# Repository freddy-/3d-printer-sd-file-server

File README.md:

# ESP8266 SD Card File Server For 3D Printer

This project mimics the file upload endpoint of OctoPrint allowing to send gcode from prusa slicer and saving direct to SD card.

It is based on ardyesp/ESPWebDAV and FYSETC/ESPWebDAV.
 
SD card is shared between ESP8266 (SPI) and 3d printer (SDIO) running Marlin firmware with a custom change. 

The ESP8266 control the SD Card detection pin from the 3D Printer board. When it receive a file upload it simulate a SD card removal from the 3D Printer and then initialize the SD Card in SPI mode. When the file upload is done it performs a power cycle of the SD Card, otherwise the SD Card wont work in SDIO mode.

This change in Marlin allow the SDIO lines from the SD card to be shared with the ESP8266. When the card is removed from the 3D Printer Marlin detects and disable the SDIO hardware and set these pins to input.

### 3D Printer
The tests were made using a Kingroon KP3S. This printer have a MakerBase Robin Nano clone board with a connector for a external SD board.

### Firmware update
Firmware update can be done via browser through url `<esp-ip>/update`

### Dependencies
- [ESP8266 Arduino](https://github.com/esp8266/Arduino)  version 3.1.2

<div style="display: flex;">

</div>

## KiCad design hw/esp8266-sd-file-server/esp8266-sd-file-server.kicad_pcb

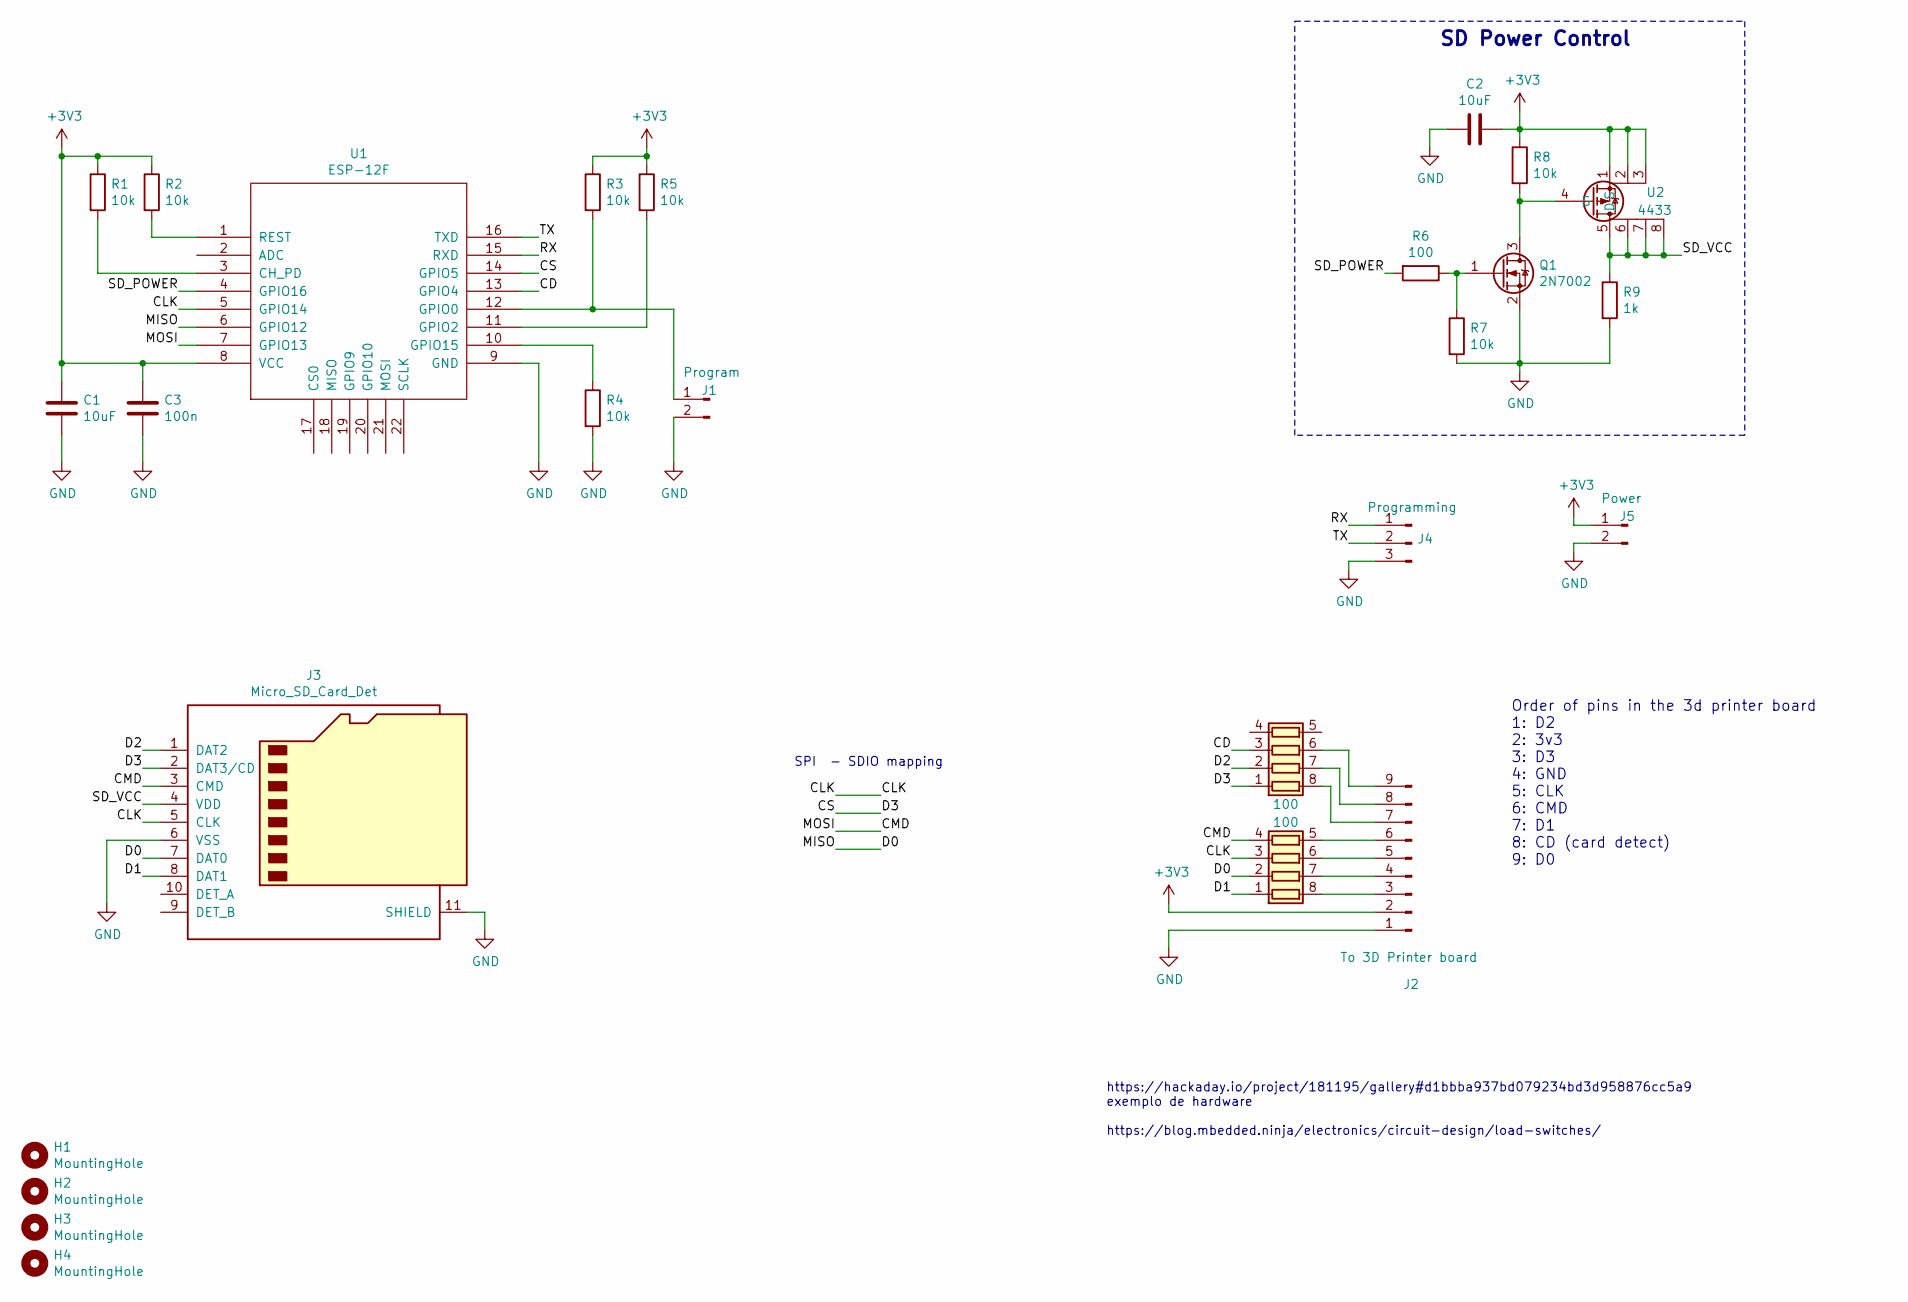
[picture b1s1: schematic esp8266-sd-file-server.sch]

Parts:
C1, C2: 10uF; C_1210_3225Metric_Pad1.42x2.65mm_HandSolder
C3: 100n; C_0805_2012Metric_Pad1.15x1.40mm_HandSolder
H1, H2, H3, H4: MountingHole; MountingHole_3mm
J1: Program; PinHeader_1x02_P2.54mm_Vertical
J2: To 3D Printer board; PinHeader_1x09_P2.54mm_Vertical
J3: Micro_SD_Card_Det; micro_sd
J4: Programming; PinHeader_1x03_P2.54mm_Vertical
J5: Power; PinHeader_1x02_P2.54mm_Vertical
Q1: 2N7002; SOT-23
R1, R2, R3, R4, R5, R7, R8: 10k; R_0603_1608Metric_Pad1.05x0.95mm_HandSolder
R6: 100; R_0603_1608Metric_Pad1.05x0.95mm_HandSolder
R9: 1k; R_0603_1608Metric_Pad1.05x0.95mm_HandSolder
RN1, RN2: 100; R_Array_Convex_4x0603
U1: ESP-12F; ESP-12E_SMD
U2: 4433; SOIC-8_3.9x4.9mm_P1.27mm

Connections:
+3V3: C1.2, C2.1, C3.2, J2.2, J5.1, R1.1, R2.1, R3.1, R5.1, R8.1, U1.8 (VCC), U2.1 (S), U2.2, U2.3
/CD: RN2.3 (R3.1), U1.13 (GPIO4)
/CLK: J3.5 (CLK), RN1.3 (R3.1), U1.5 (GPIO14)
/CMD: J3.3 (CMD), RN1.4 (R4.1), U1.7 (GPIO13)
/CS: J3.2 (DAT3/CD), RN2.1 (R1.1), U1.14 (GPIO5)
/D0: J3.7 (DAT0), RN1.2 (R2.1), U1.6 (GPIO12)
/D1: J3.8 (DAT1), RN1.1 (R1.1)
/D2: J3.1 (DAT2), RN2.2 (R2.1)
/RX: J4.1, U1.15 (RXD)
/SD_POWER: R6.2, U1.4 (GPIO16)
/SD_VCC: J3.4 (VDD), R9.1, U2.5 (D), U2.6, U2.7, U2.8
/TX: J4.2, U1.16 (TXD)
GND: C1.1, C2.2, C3.1, J1.2, J2.1, J3.6 (VSS), J3.11 (SHIELD), J4.3, J5.2, Q1.2 (S), R4.2, R7.2, R9.2, U1.9 (GND)
unnamed: J1.1, R3.2, U1.12 (GPIO0)
unnamed: J2.3, RN1.8 (R1.2)
unnamed: J2.4, RN1.7 (R2.2)
unnamed: J2.5, RN1.6 (R3.2)
unnamed: J2.6, RN1.5 (R4.2)
unnamed: J2.7, RN2.8 (R1.2)
unnamed: J2.8, RN2.7 (R2.2)
unnamed: J2.9, RN2.6 (R3.2)
unnamed: Q1.1 (G), R6.1, R7.1
unnamed: Q1.3 (D), R8.2, U2.4 (G)
unnamed: R1.2, U1.3 (CH_PD)
unnamed: R2.2, U1.1 (REST)
unnamed: R4.1, U1.10 (GPIO15)
unnamed: R5.2, U1.11 (GPIO2)

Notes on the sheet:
SD Power Control
https://hackaday.io/project/181195/gallery#d1bbba937bd079234bd3d958876cc5a9 exemplo de hardware https://blog.mbedded.ninja/electronics/circuit-design/load-switches/
SPI - SDIO mapping
Order of pins in the 3d printer board 1: D2 2: 3v3 3: D3 4: GND 5: CLK 6: CMD 7: D1 8: CD (card detect) 9: D0

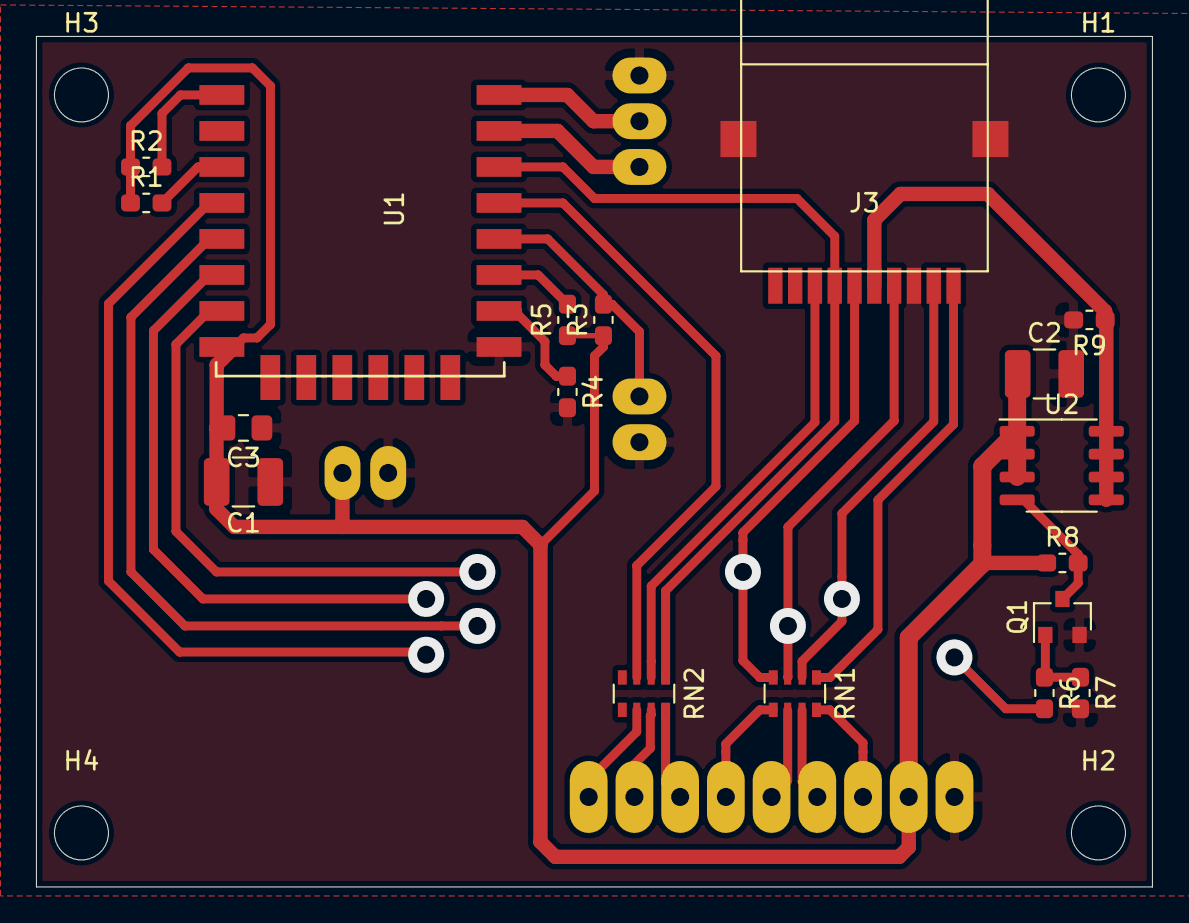
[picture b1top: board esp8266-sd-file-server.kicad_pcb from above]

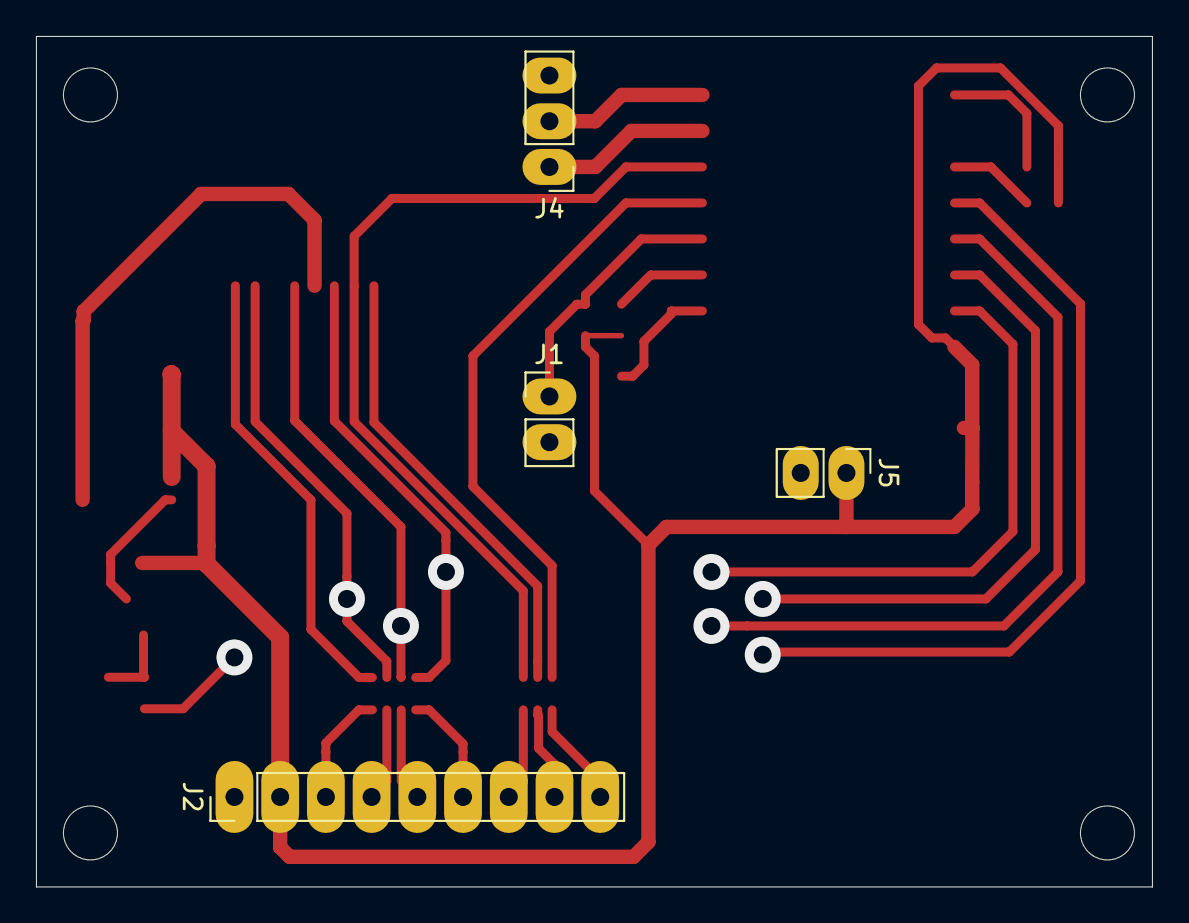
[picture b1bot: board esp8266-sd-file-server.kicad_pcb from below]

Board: 2 copper layers, 62.0 x 47.2 mm, 26 parts (4 on the bottom side), 27 nets.

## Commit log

2024-12-16 Update code to use latest esp8266 arduino version
2024-12-16 Organize files
2025-09-17 Refactor http routing
